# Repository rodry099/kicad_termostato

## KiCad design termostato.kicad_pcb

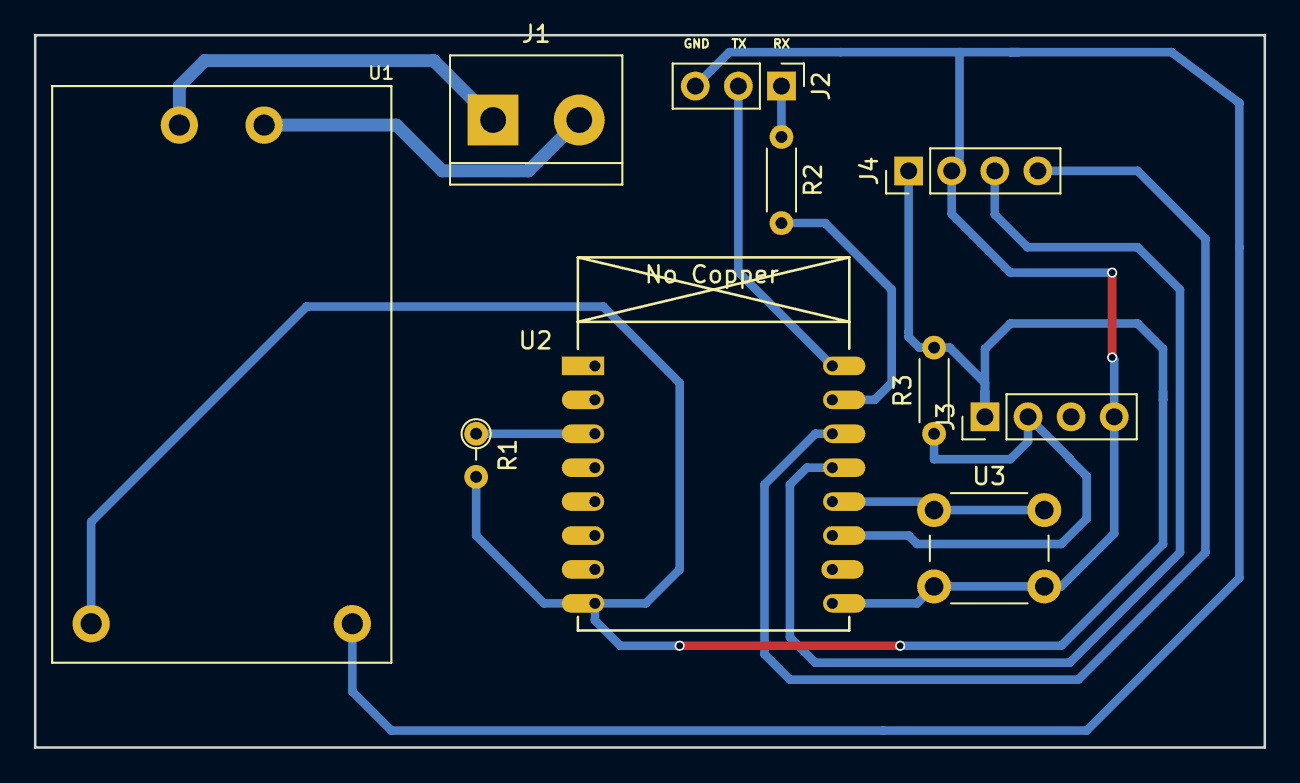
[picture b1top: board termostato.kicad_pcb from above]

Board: 2 copper layers, 72.5 x 42.0 mm, 10 parts (0 on the bottom side), 12 nets.

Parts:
J1: Conn_01x02_Female; TerminalBlock_bornier-2_P5.08mm
J2: Conn_01x03_Female; Socket_Strip_Straight_1x03_Pitch2.54mm
J3, J4: Conn_01x04_Female; Socket_Strip_Straight_1x04_Pitch2.54mm
R1: 10K; R_Axial_DIN0204_L3.6mm_D1.6mm_P2.54mm_Vertical
R2: 180; R_Axial_DIN0204_L3.6mm_D1.6mm_P5.08mm_Horizontal
R3: 4K7; R_Axial_DIN0204_L3.6mm_D1.6mm_P5.08mm_Horizontal
U1: HLK-PM03
U2: ESP-07v2
U3: pulsador; SW_PUSH_6mm

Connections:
GND: J2.3, J3.4, J4.2, U1.3, U2.9, U3.2
unnamed: J1.1, U1.2
unnamed: J1.2, U1.1
unnamed: J2.1, R2.1
unnamed: J2.2, U2.16
unnamed: J3.1, J4.1, R1.2, R3.2, U1.4, U2.8
unnamed: J3.2, R3.1
unnamed: R1.1, U2.3
unnamed: R2.2, U2.15
unnamed: U2.12, U3.1
SCL: J4.3, U2.13
SDA: J4.4, U2.14

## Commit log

2017-12-29 primer commit
2022-08-08 Add .circleci/config.yml
